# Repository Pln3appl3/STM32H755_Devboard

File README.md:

# STM32H755_Devboard
A custom devboard using the STM32H755 chip that I built to be used to prototype and test complex robotics machines I plan to build in the future and consists of MicroSD card slot, CAN-FD inbuilt, USB-C, SWD Debug header, boot and reset buttons to flash with USB-C, and external flash.

## Why did I make this?
I made this as I wanted a high-end microcontroller that has a dual core processor and has multiple functionalities, and that eventually led to me making this custom devboard that I plan on using to test prototypes for any complex robots I want to make and not worry about being bottlenecked by the microcontroller.

## Pictures

## Footprint Pictures
### Top Layer

### GND Layer

### Power Layer

### Bottom Layer

### BOM
| Component                 | Amount | Price per unit | Total Price | Purpose                                                                     | Link                                                                                                                                                                                                                                                                       |
|---------------------------|--------|----------------|-------------|-----------------------------------------------------------------------------|----------------------------------------------------------------------------------------------------------------------------------------------------------------------------------------------------------------------------------------------------------------------------|
| STM32H755ZIT3             | 1      | $20.11         | $20.11      | MCU for the board                                                           | https://www.digikey.com/en/products/detail/stmicroelectronics/STM32H755ZIT3/18086228                                                                                                                                                                                       |
| TYPE-C-16P-3MD            | 1      | $0.19          | $1.90       | USB-C data and power (Had to buy 10 as that was the minimum purchase amount | https://www.digikey.com/en/products/detail/shenzhen-shouhan-technology-co-ltd/type-c-16p-3md/29627623                                                                                                                                                                      |
| USBLC6-2SC6Y              | 1      | $0.67          | $0.67       | ESD protection for data lines                                               | https://www.digikey.com/en/products/detail/stmicroelectronics/usblc6-2sc6y/2819177                                                                                                                                                                                         |
| SSC54-E3/57T              | 2      | $1.05          | $2.10       | Diode to prevent reverse current                                            | https://www.digikey.com/en/products/detail/vishay-general-semiconductor-diodes-division/ssc54-e3-57t/1091564                                                                                                                                                               |
| TPS75733KTTR              | 1      | $11.26         | $11.26      | 3.3V LDO                                                                    | https://www.digikey.com/en/products/detail/texas-instruments/tps75733kttr/1673150                                                                                                                                                                                          |
| TCAN1044VDRBRQ1           | 1      | $1.86          | $1.86       | CAN-FD Transceiver                                                          | https://www.digikey.com/en/products/detail/texas-instruments/tcan1044vdrbrq1/13245687                                                                                                                                                                                      |
| ESD2CAN24DCKRQ1           | 1      | $0.40          | $0.40       | ESD protection for CAN-FD                                                   | https://www.digikey.com/en/products/detail/texas-instruments/esd2can24dckrq1/16982070                                                                                                                                                                                      |
| TSX-3225_25.0000MF20X-AJ0 | 1      | $0.37          | $0.37       | 25MHz crystal                                                               | https://www.digikey.com/en/products/detail/epson/TSX-3225-25-0000MF20X-AJ0/5168442?s=N4IgTCBcDaICoGUAaBaAzGMBWA%2BtgdAAzGECyAYmIagIIBShIAugL5A                                                                                                                             |
| W25Q256JVEIQ TR           | 1      | $6.08          | $6.08       | External Flash                                                              | https://www.digikey.com/en/products/detail/winbond-electronics/w25q256jveiq-tr/5803969                                                                                                                                                                                     |
| MSD-1-A                   | 1      | $0.38          | $0.38       | MicroSD card port                                                           | https://www.digikey.com/en/products/detail/same-sky-formerly-cui-devices/msd-1-a/21799641                                                                                                                                                                                  |
| EVP-AWBD4A                | 2      | $0.30          | $0.60       | Button for boot and reset                                                   | https://www.digikey.com/en/products/detail/panasonic-industry/EVP-AWBD4A/8568273                                                                                                                                                                                           |
| GRM155Z71A225KE44D        | 2      | $0.15          | $0.30       | VCAP Capacitors with under .1 Ohm ESR                                       | https://www.digikey.com/en/products/detail/murata-electronics/GRM155Z71A225KE44D/10264880                                                                                                                                                                                  |
| C2012X7R1A475K085AC       | 4      | $0.27          | $1.08       | Buk and filtering capacitor                                                 | https://www.digikey.com/en/products/detail/tdk/C2012X7R1A475K085AC/3951763                                                                                                                                                                                                 |
| GRT188R61C106KE13D        | 3      | $0.29          | $0.87       | Bulk Capacitor                                                              | https://www.digikey.com/en/products/detail/murata-electronics/GRT188R61C106KE13D/5416739                                                                                                                                                                                   |
| KAM05CR71A105KH           | 4      | $0.17          | $0.68       | Decoupling/Filtering capacitor                                              | https://www.digikey.com/en/products/detail/kyocera-avx/KAM05CR71A105KH/22198421                                                                                                                                                                                            |
| CC0402JRX7R8BB104         | 31     | $0.05          | $1.58       | Decoupling capacitor                                                        | https://www.digikey.com/en/products/detail/yageo/CC0402JRX7R8BB104/11491448                                                                                                                                                                                                |
| C0402C100F4HACAUTO        | 2      | $0.18          | $0.36       | Crystal load capacitor                                                      | https://www.digikey.com/en/products/detail/kemet/C0402C100F4HACAUTO/7955039                                                                                                                                                                                                |
| T495D476K025ATE250        | 1      | $2.36          | $2.36       | LDO output bulk capacitor                                                   | https://www.digikey.com/en/products/detail/kemet/T495D476K025ATE250/3760574                                                                                                                                                                                                |
| BLM18SG121TN1D            | 1      | $0.14          | $0.14       | Ferrite bead for analog filtering                                           | https://www.digikey.com/en/products/detail/murata-electronics/blm18sg121tn1d/1016155                                                                                                                                                                                       |
| RC0201JR-070RL            | 1      | $0.10          | $0.10       | Resistor Jumper for VREF+                                                   | https://www.digikey.com/en/products/detail/yageo/RC0201JR-070RL/1948898                                                                                                                                                                                                    |
| RC0201FR-0710KL           | 10     | $0.03          | $0.34       | 10K ohm Pull-up resistor                                                    | https://www.digikey.com/en/products/detail/yageo/RC0201FR-0710KL/1948870                                                                                                                                                                                                   |
| RC0201FR-0733RL           | 2      | $0.10          | $0.20       | 33 Ohm dampening resistor                                                   | https://www.digikey.com/en/products/detail/yageo/RC0201FR-0733RL/1948893                                                                                                                                                                                                   |
| RC0201FR-0722RL           | 12     | $0.03          | $0.41       | 22 Ohm dampening resistor                                                   | https://www.digikey.com/en/products/detail/yageo/RC0201FR-0722RL/5280378                                                                                                                                                                                                   |
| RC0201FR-07330RL          | 2      | $0.10          | $0.20       | 330 Ohm current limiting resistor                                           | https://www.digikey.com/en/products/detail/yageo/RC0201FR-07330RL/5280464                                                                                                                                                                                                  |
| RC0201FR-135K1L           | 2      | $0.10          | $0.20       | USB-C detection pull-down resistor                                          | https://www.digikey.com/en/products/detail/yageo/RC0201FR-135K1L/17017100                                                                                                                                                                                                  |
| RC0201FR-0760R4L          | 2      | $0.10          | $0.20       | CAN-FD Termination resistors                                                | https://www.digikey.com/en/products/detail/yageo/RC0201FR-0760R4L/5280609                                                                                                                                                                                                  |
| XZMDK68W-2                | 1      | $0.23          | $0.23       | Debug LED                                                                   | https://www.digikey.com/en/products/detail/sunled/XZMDK68W-2/4745956                                                                                                                                                                                                       |
| XZVG68W-2                 | 1      | $0.26          | $0.26       | Debug LED                                                                   | https://www.digikey.com/en/products/detail/sunled/XZVG68W-2/4745975                                                                                                                                                                                                        |
| M50-3530242               | 39     | $0.08          | $3.28       | Headers                                                                     | https://www.digikey.com/en/products/detail/harwin-inc/M50-3530242/7044013                                                                                                                                                                                                  |
| 1729131                   | 1      | $1.44          | $1.44       | CAN-FD Terminal Block                                                       | https://www.digikey.com/en/products/detail/phoenix-contact/1729131/260616?gclsrc=aw.ds&gad_source=1&gad_campaignid=20470400566&gbraid=0AAAAADrbLlj-SwBWNmRjWltE4mZiVSUbP&gclid=CjwKCAjwyOzSBhBTEiwAmxvJ-i2JYjfEpwLhNZfRW2nS4iQSrP2ChCn7KzhPh37FH3seILU0pkDq6RoCWAIQAvD_BwE |
|PCB                        |5       | $15.32        | $76.60       |                                                                            ||
| Total                     |        |                | $130.36     |                                                                             |                                                                                                                                                                                                                                                                            |

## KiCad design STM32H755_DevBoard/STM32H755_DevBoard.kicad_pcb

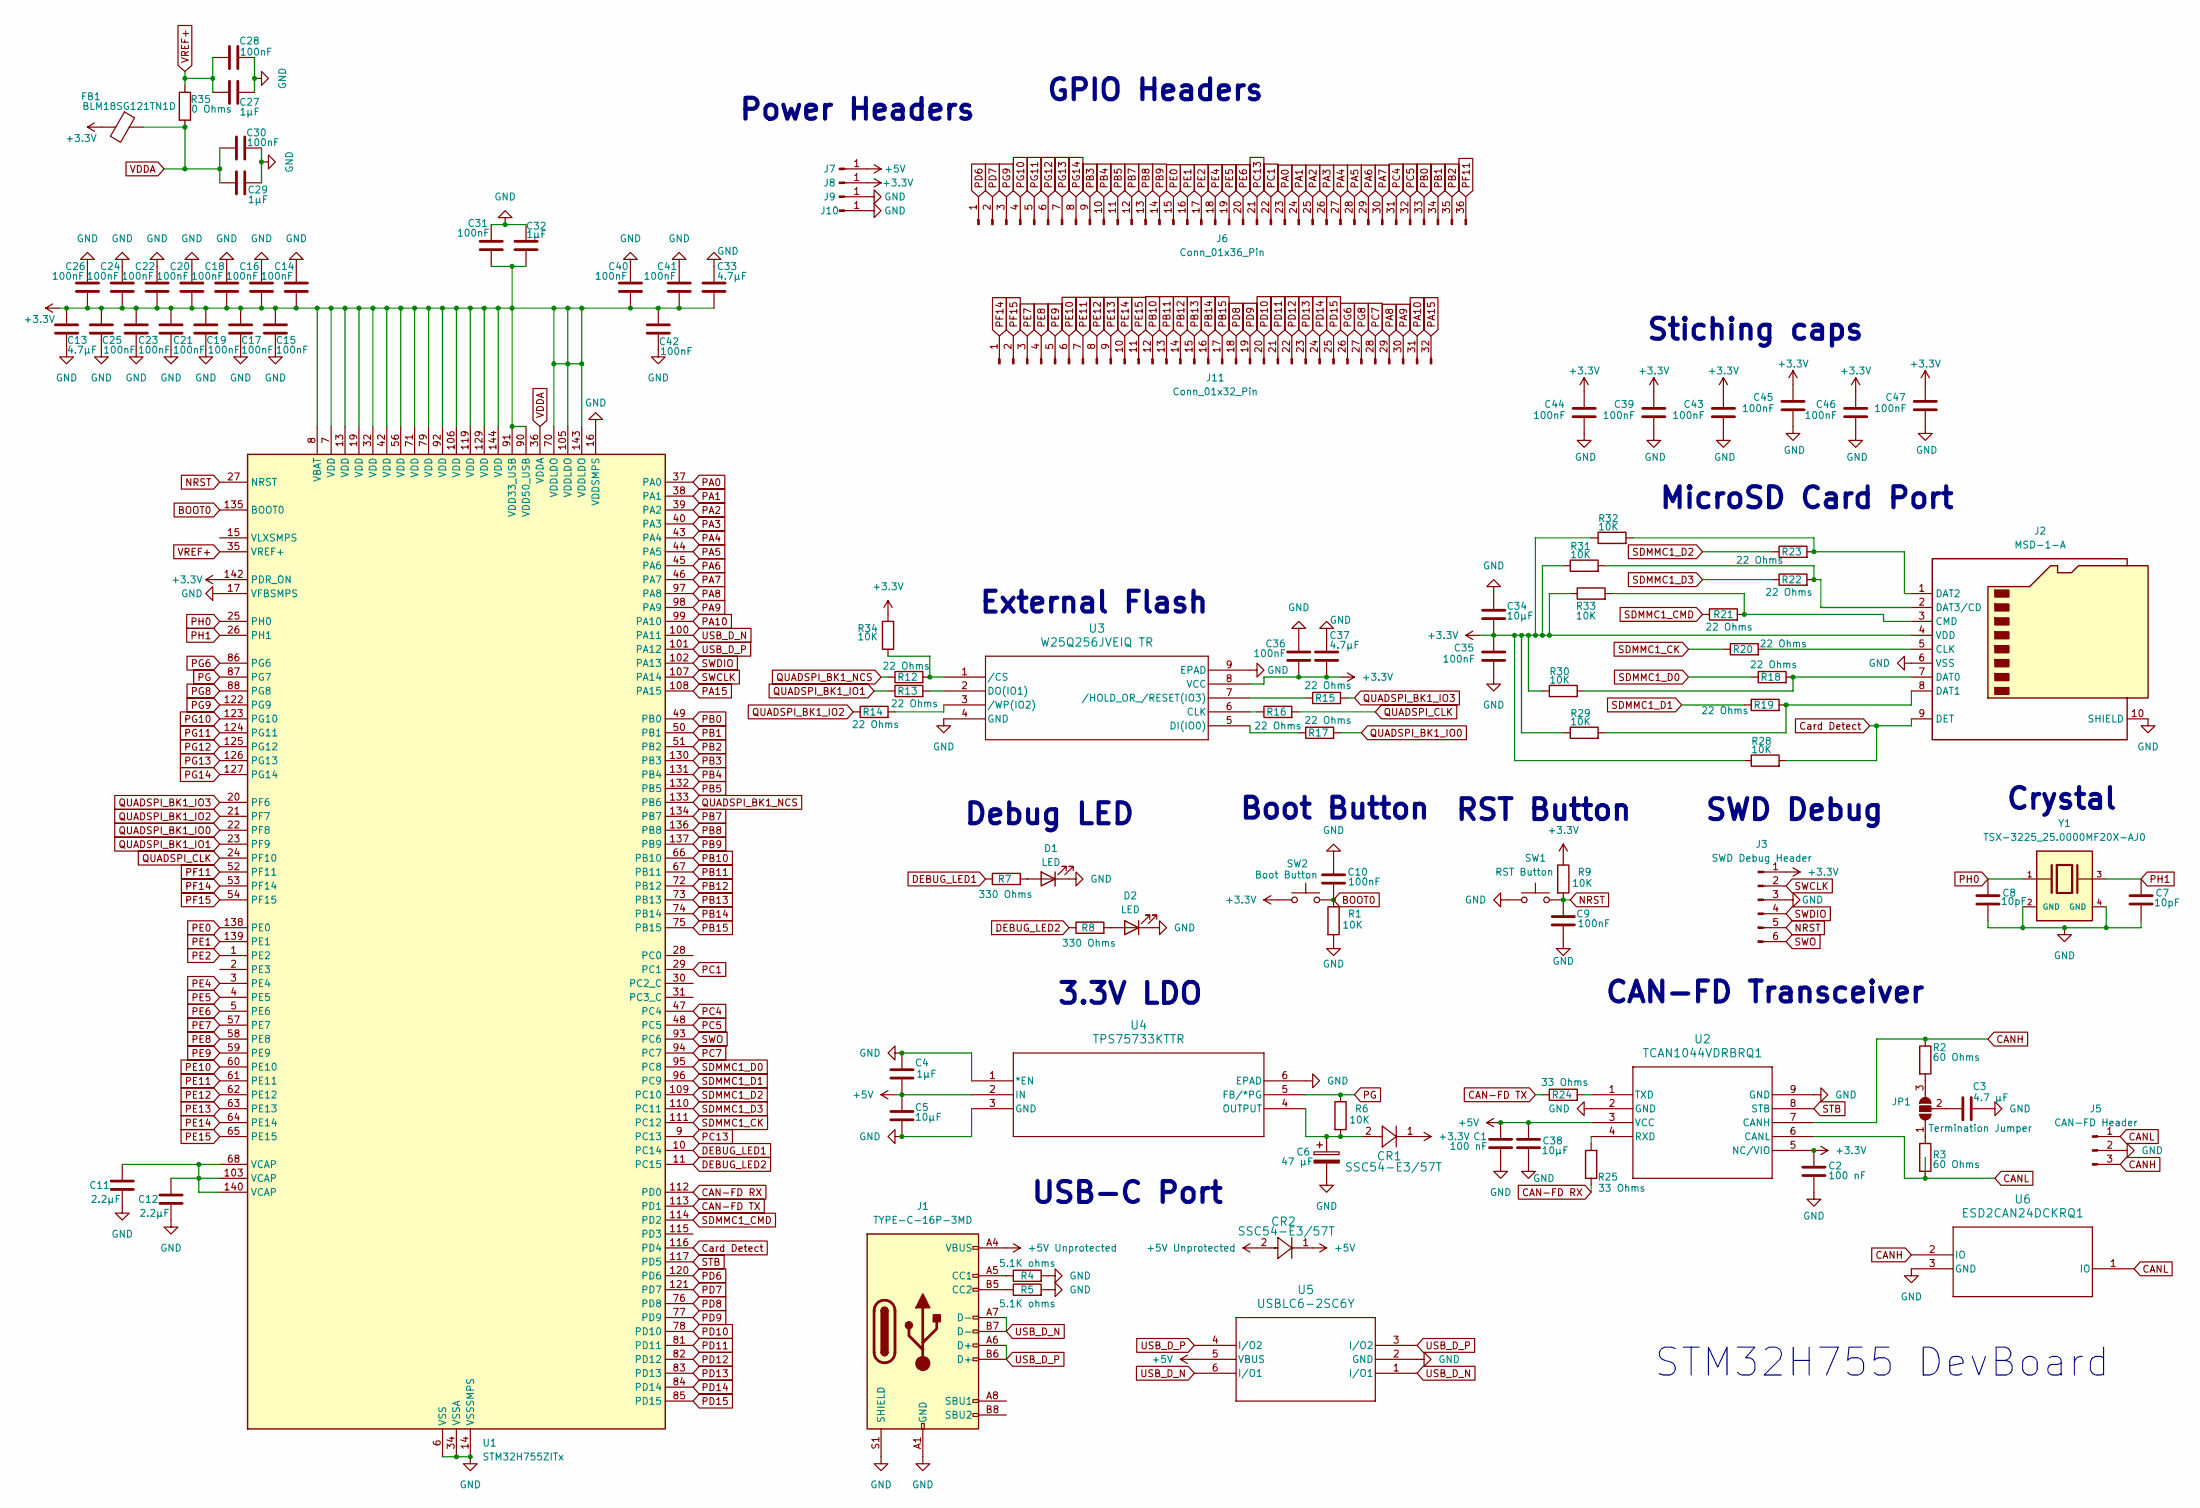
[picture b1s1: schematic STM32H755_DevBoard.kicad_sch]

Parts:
C1, C2: 100 nF; C_0402_1005Metric_Pad0.74x0.62mm_HandSolder
C3: 4.7 μF; C_0805_2012Metric_Pad1.18x1.45mm_HandSolder
C4, C27, C29, C32: 1µF; C_0402_1005Metric_Pad0.74x0.62mm_HandSolder
C5, C34, C38: 10µF; C_0603_1608Metric_Pad1.08x0.95mm_HandSolder
C6: 47 μF; CP_EIA-7343-31_Kemet-D
C7, C8: 10pF; C_0402_1005Metric_Pad0.74x0.62mm_HandSolder
C9, C10, C14, C15, C16, C17, C18, C19, C20, C21, C22, C23, C24, C25, C26, C28, C30, C31, C35, C36, C39, C40, C41, C42, C43, C44, C45, C46, C47: 100nF; C_0402_1005Metric_Pad0.74x0.62mm_HandSolder
C11, C12: 2.2µF; C_0402_1005Metric_Pad0.74x0.62mm_HandSolder
C13, C33, C37: 4.7µF; C_0805_2012Metric_Pad1.18x1.45mm_HandSolder
CR1, CR2: SSC54-E3/57T; D_SMC
D1, D2: LED; LED_0402_1005Metric_Pad0.77x0.64mm_HandSolder
FB1: BLM18SG121TN1D; L_0603_1608Metric_Pad1.05x0.95mm_HandSolder
J1: TYPE-C-16P-3MD; KINGHELM_KH-TYPE-C-16P
J2: MSD-1-A; CUI_MSD-1-A
J3: SWD Debug Header; PinHeader_1x06_P2.54mm_Vertical
J5: CAN-FD Header; TerminalBlock_Phoenix_MKDS-1,5-3-5.08_1x03_P5.08mm_Horizont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
J6: Conn_01x36_Pin; PinHeader_2x18_P2.54mm_Vertical
J7, J8, J9, J10: Conn_01x01_Pin; PinHeader_1x01_P2.54mm_Vertical
J11: Conn_01x32_Pin; PinHeader_2x16_P2.54mm_Vertical
JP1: Termination Jumper; SolderJumper-3_P2.0mm_Open_TrianglePad1.0x1.5mm
R1, R6, R9, R28, R29, R30, R31, R32, R33, R34: 10K; R_0201_0603Metric_Pad0.64x0.40mm_HandSolder
R2, R3: 60 Ohms; R_0201_0603Metric_Pad0.64x0.40mm_HandSolder
R4, R5: 5.1K ohms; R_0201_0603Metric_Pad0.64x0.40mm_HandSolder
R7, R8: 330 Ohms; R_0201_0603Metric_Pad0.64x0.40mm_HandSolder
R12, R13, R14, R15, R16, R17, R18, R19, R20, R21, R22, R23: 22 Ohms; R_0201_0603Metric_Pad0.64x0.40mm_HandSolder
R24, R25: 33 Ohms; R_0201_0603Metric_Pad0.64x0.40mm_HandSolder
R35: 0 Ohms; R_0201_0603Metric_Pad0.64x0.40mm_HandSolder
SW1: RST Button; SW_EVP-AWBD4A
SW2: Boot Button; SW_EVP-AWBD4A
U1: STM32H755ZITx; LQFP-144_20x20mm_P0.5mm
U2: TCAN1044VDRBRQ1; SON8_DRB_TEX-M
U3: W25Q256JVEIQ TR; WSON8_E_WIN-M
U4: TPS75733KTTR; KTT5_6P22X6P86-M
U5: USBLC6-2SC6Y; SOT23-6L_STM-M
U6: ESD2CAN24DCKRQ1; SOT-SC70_3_DCK_TEX-M
Y1: TSX-3225_25.0000MF20X-AJ0; Crystal_SMD_3225-4Pin_3.2x2.5mm; PARTREV N/A

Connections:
+3.3V: C2.1, C13.1, C14.1, C15.1, C16.1, C17.1, C18.1, C19.1, C20.1, C21.1, C22.1, C23.1, C24.1, C25.1, C26.1, C31.1, C32.1, C33.1, C34.2, C35.1, C36.1, C37.1, C39.1, C40.1, C41.1, C42.1, C43.1, C44.1, C45.1, C46.1, C47.1, CR1.1, FB1.2, J2.4 (VDD), J3.1, J8.1, R9.1, R28.1, R29.1, R30.1, R31.1, R32.1, R33.1, R34.2, SW2.1, U1.7 (VDD), U1.8 (VBAT), U1.13 (VDD), U1.19 (VDD), U1.32 (VDD), U1.42 (VDD), U1.56 (VDD), U1.70 (VDDLDO), U1.71 (VDD), U1.79 (VDD), U1.90 (VDD50_USB), U1.91 (VDD33_USB), U1.92 (VDD), U1.105 (VDDLDO), U1.106 (VDD), U1.119 (VDD), U1.129 (VDD), U1.142 (PDR_ON), U1.143 (VDDLDO), U1.144 (VDD), U2.5 (NC/VIO), U3.8 (VCC)
+5V: C1.1, C4.2, C5.1, C38.2, CR2.1, J7.1, U2.3 (VCC), U4.2 (IN), U5.5 (VBUS)
+5V Unprotected: CR2.2, J1.A4 (VBUS), J1.B9 (VBUS)
BOOT0: C10.1, R1.1, SW2.2, U1.135 (BOOT0)
CAN-FD RX: R25.1, U1.112 (PD0)
CAN-FD TX: R24.1, U1.113 (PD1)
CANH: J5.3, R2.1, U2.7 (CANH), U6.2 (IO)
CANL: J5.1, R3.2, U2.6 (CANL), U6.1 (IO)
Card Detect: J2.9 (DET), R28.2, U1.116 (PD4)
DEBUG_LED1: R7.1, U1.10 (PC14)
DEBUG_LED2: R8.1, U1.11 (PC15)
GND: C1.2, C2.2, C3.2, C4.1, C5.2, C6.2, C7.2, C8.2, C9.2, C10.2, C11.2, C12.2, C13.2, C14.2, C15.2, C16.2, C17.2, C18.2, C19.2, C20.2, C21.2, C22.2, C23.2, C24.2, C25.2, C26.2, C27.2, C28.2, C29.2, C30.2, C31.2, C32.2, C33.2, C34.1, C35.2, C36.2, C37.2, C38.1, C39.2, C40.2, C41.2, C42.2, C43.2, C44.2, C45.2, C46.2, C47.2, D1.1 (K), D2.1 (K), J1.A1 (GND), J1.A12 (GND), J1.S1 (SHIELD), J2.6 (VSS), J2.10 (SHIELD), J3.3, J5.2, J9.1, J10.1, R1.2, R4.2, R5.2, SW1.1, U1.6 (VSS), U1.12 (VSS), U1.14 (VSSSMPS), U1.16 (VDDSMPS), U1.17 (VFBSMPS), U1.18 (VSS), U1.33 (VSS), U1.34 (VSSA), U1.41 (VSS), U1.55 (VSS), U1.69 (VSS), U1.80 (VSS), U1.89 (VSS), U1.104 (VSS), U1.118 (VSS), U1.128 (VSS), U1.141 (VSS), U2.2 (GND), U2.9 (GND), U3.4 (GND), U3.9 (EPAD), U4.1 (*EN), U4.3 (GND), U4.6 (EPAD), U5.2 (GND), U6.3 (GND), Y1.2 (GND), Y1.4 (GND)
NRST: C9.1, J3.5, R9.2, SW1.2, U1.27 (NRST)
unnamed: C11.1, C12.1, U1.68 (VCAP), U1.103 (VCAP), U1.140 (VCAP)
unnamed: D1.2 (A), R7.2
unnamed: D2.2 (A), R8.2
unnamed: J1.A5 (CC1), R4.1
unnamed: J1.B5 (CC2), R5.1
unnamed: J2.5 (CLK), R20.2
unnamed: J2.3 (CMD), R21.2, R33.2
unnamed: J2.7 (DAT0), R18.2, R30.2
unnamed: J2.8 (DAT1), R19.2, R29.2
unnamed: J2.1 (DAT2), R23.2, R32.2
unnamed: J2.2 (DAT3/CD), R22.2, R31.2
unnamed: JP1.1 (A), R3.1
unnamed: JP1.3 (B), R2.2
unnamed: C3.1, JP1.2 (C)
unnamed: R25.2, U2.4 (RXD)
unnamed: R24.2, U2.1 (TXD)
unnamed: R16.1, U3.6 (CLK)
unnamed: R17.1, U3.5 (DI(IO0))
unnamed: R13.2, U3.2 (DO(IO1))
unnamed: R12.2, R34.1, U3.1 (/CS)
unnamed: R15.1, U3.7 (/HOLD_OR_/RESET(IO3))
unnamed: R14.2, U3.3 (/WP(IO2))
unnamed: C6.1, CR1.2, R6.2, U4.4 (OUTPUT)
PA0: J6.23, U1.37 (PA0)
PA1: J6.24, U1.38 (PA1)
PA2: J6.25, U1.39 (PA2)
PA3: J6.26, U1.40 (PA3)
PA4: J6.27, U1.43 (PA4)
PA5: J6.28, U1.44 (PA5)
PA6: J6.29, U1.45 (PA6)
PA7: J6.30, U1.46 (PA7)
PA8: J11.29, U1.97 (PA8)
PA9: J11.30, U1.98 (PA9)
PA10: J11.31, U1.99 (PA10)
PA15: J11.32, U1.108 (PA15)
PB0: J6.33, U1.49 (PB0)
PB1: J6.34, U1.50 (PB1)
PB2: J6.35, U1.51 (PB2)
PB3: J6.9, U1.130 (PB3)
PB4: J6.10, U1.131 (PB4)
PB5: J6.11, U1.132 (PB5)
PB7: J6.12, U1.134 (PB7)
PB8: J6.13, U1.136 (PB8)
PB9: J6.14, U1.137 (PB9)
PB10: J11.12, U1.66 (PB10)
PB11: J11.13, U1.67 (PB11)
PB12: J11.14, U1.72 (PB12)
PB13: J11.15, U1.73 (PB13)
PB14: J11.16, U1.74 (PB14)
PB15: J11.17, U1.75 (PB15)
PC1: J6.22, U1.29 (PC1)
PC4: J6.31, U1.47 (PC4)
PC5: J6.32, U1.48 (PC5)
PC7: J11.28, U1.94 (PC7)
PC13: J6.21, U1.9 (PC13)
PD6: J6.1, U1.120 (PD6)
PD7: J6.2, U1.121 (PD7)
PD8: J11.18, U1.76 (PD8)
PD9: J11.19, U1.77 (PD9)
PD10: J11.20, U1.78 (PD10)
PD11: J11.21, U1.81 (PD11)
PD12: J11.22, U1.82 (PD12)
PD13: J11.23, U1.83 (PD13)
PD14: J11.24, U1.84 (PD14)
PD15: J11.25, U1.85 (PD15)
PE0: J6.15, U1.138 (PE0)
PE1: J6.16, U1.139 (PE1)
PE2: J6.17, U1.1 (PE2)
PE4: J6.18, U1.3 (PE4)
PE5: J6.19, U1.4 (PE5)
PE6: J6.20, U1.5 (PE6)
PE7: J11.3, U1.57 (PE7)
PE8: J11.4, U1.58 (PE8)
PE9: J11.5, U1.59 (PE9)
PE10: J11.6, U1.60 (PE10)
PE11: J11.7, U1.61 (PE11)
PE12: J11.8, U1.62 (PE12)
PE13: J11.9, U1.63 (PE13)
PE14: J11.10, U1.64 (PE14)
PE15: J11.11, U1.65 (PE15)
PF11: J6.36, U1.52 (PF11)
PF14: J11.1, U1.53 (PF14)
PF15: J11.2, U1.54 (PF15)
PG: R6.1, U1.87 (PG7), U4.5 (FB/*PG)
PG6: J11.26, U1.86 (PG6)
PG8: J11.27, U1.88 (PG8)
PG9: J6.3, U1.122 (PG9)
PG10: J6.4, U1.123 (PG10)
PG11: J6.5, U1.124 (PG11)
PG12: J6.6, U1.125 (PG12)
PG13: J6.7, U1.126 (PG13)
PG14: J6.8, U1.127 (PG14)
PH0: C8.1, U1.25 (PH0), Y1.1
PH1: C7.1, U1.26 (PH1), Y1.3
QUADSPI_BK1_IO0: R17.2, U1.22 (PF8)
QUADSPI_BK1_IO1: R13.1, U1.23 (PF9)
QUADSPI_BK1_IO2: R14.1, U1.21 (PF7)
QUADSPI_BK1_IO3: R15.2, U1.20 (PF6)
QUADSPI_BK1_NCS: R12.1, U1.133 (PB6)
QUADSPI_CLK: R16.2, U1.24 (PF10)
SDMMC1_CK: R20.1, U1.111 (PC12)
SDMMC1_CMD: R21.1, U1.114 (PD2)
SDMMC1_D0: R18.1, U1.95 (PC8)
SDMMC1_D1: R19.1, U1.96 (PC9)
SDMMC1_D2: R23.1, U1.109 (PC10)
SDMMC1_D3: R22.1, U1.110 (PC11)
STB: U1.117 (PD5), U2.8 (STB)
SWCLK: J3.2, U1.107 (PA14)
SWDIO: J3.4, U1.102 (PA13)
SWO: J3.6, U1.93 (PC6)
USB_D_N: J1.A7 (D-), J1.B7 (D-), U1.100 (PA11), U5.1 (I/O1), U5.6 (I/O1)
USB_D_P: J1.A6 (D+), J1.B6 (D+), U1.101 (PA12), U5.3 (I/O2), U5.4 (I/O2)
VDDA: C29.1, C30.1, FB1.1, R35.2, U1.36 (VDDA)
VREF+: C27.1, C28.1, R35.1, U1.35 (VREF+)

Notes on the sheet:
3.3V LDO
RST Button
Stiching caps
GPIO Headers
Power Headers
Crystal
SWD Debug
CAN-FD Transceiver
USB-C Port
External Flash
MicroSD Card Port
STM32H755 DevBoard
Boot Button
Debug LED

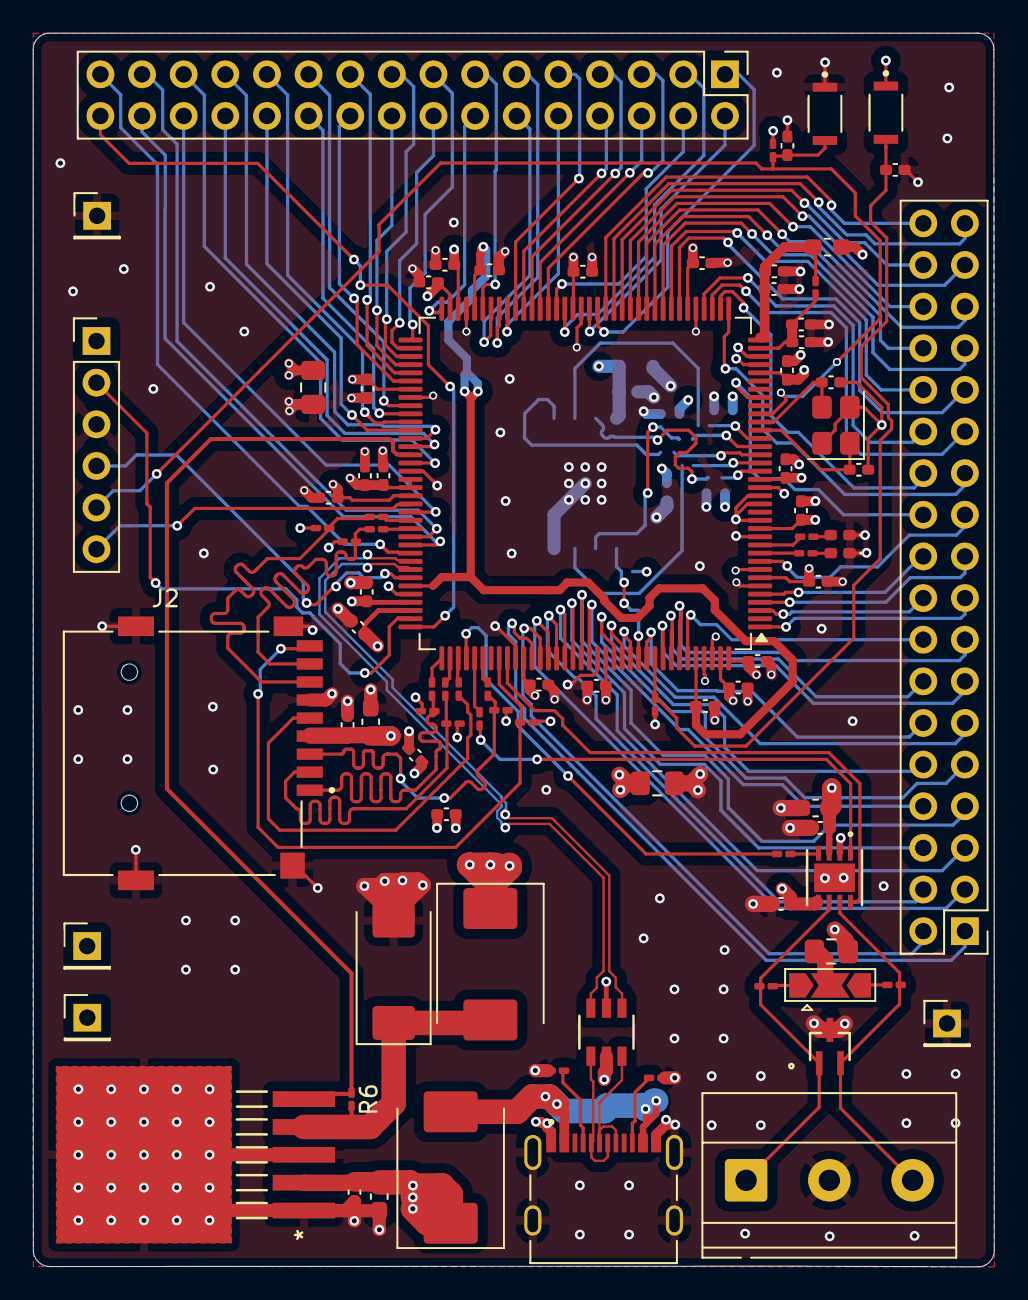
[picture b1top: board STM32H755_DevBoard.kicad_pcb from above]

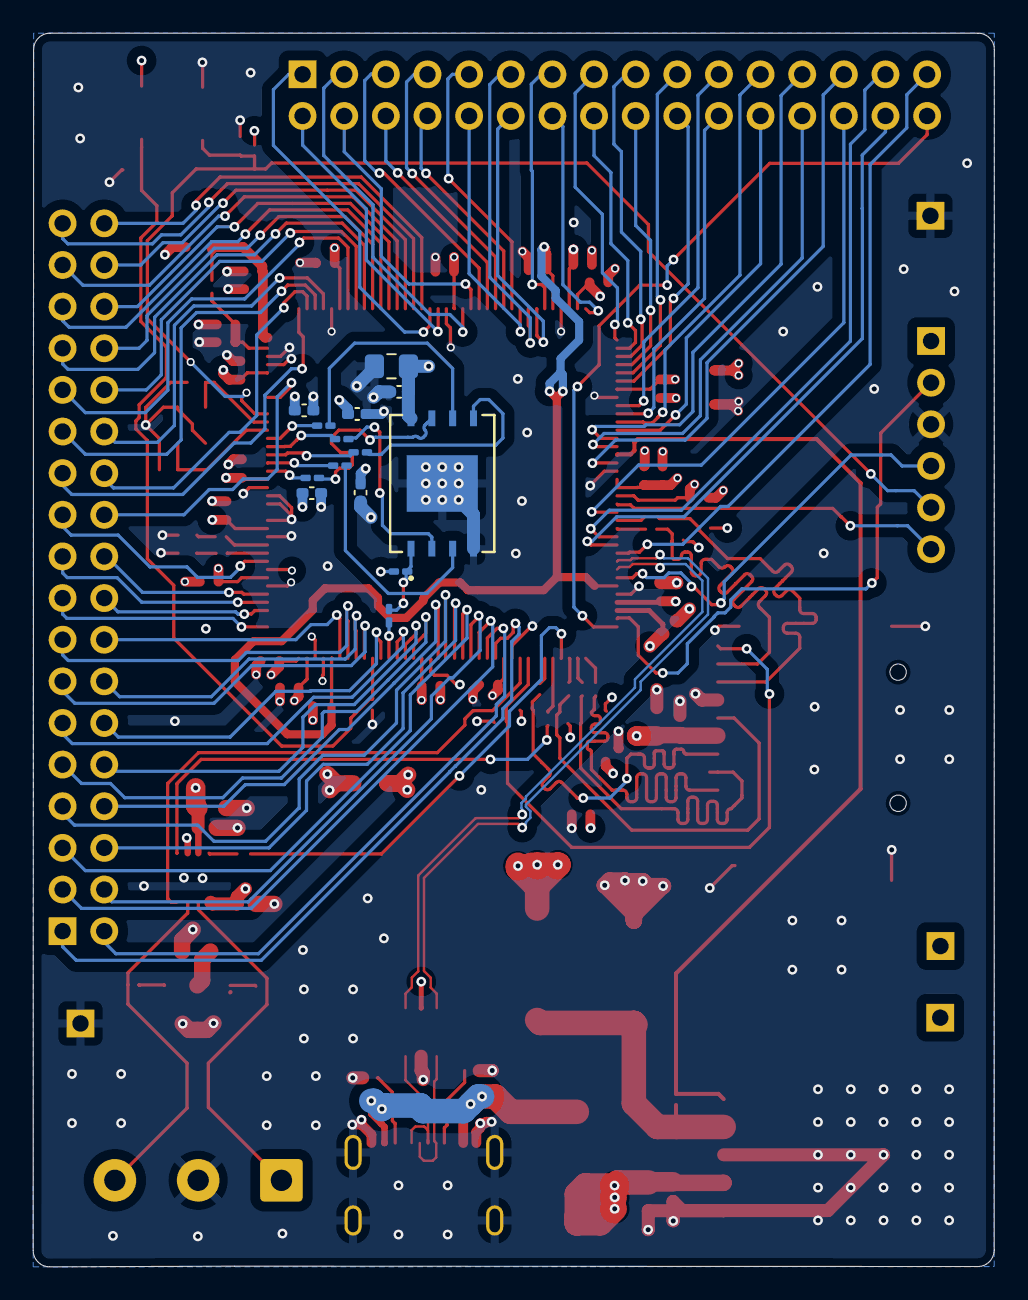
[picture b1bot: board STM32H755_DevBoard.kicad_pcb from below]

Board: 4 copper layers, 58.6 x 75.3 mm, 103 parts (14 on the bottom side), 127 nets.
